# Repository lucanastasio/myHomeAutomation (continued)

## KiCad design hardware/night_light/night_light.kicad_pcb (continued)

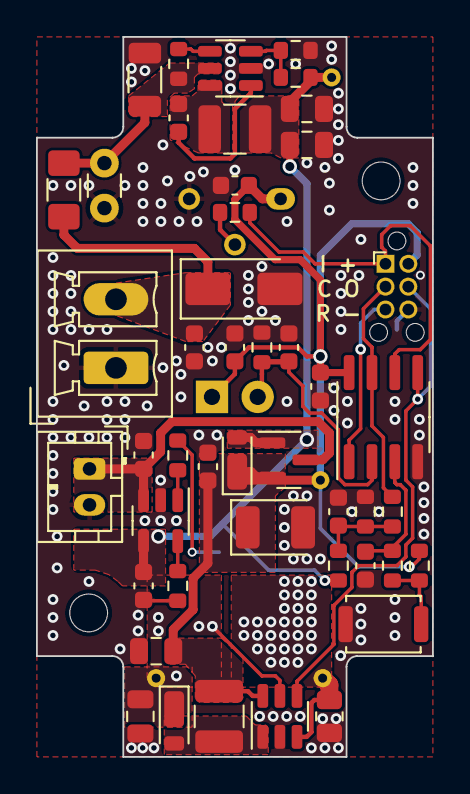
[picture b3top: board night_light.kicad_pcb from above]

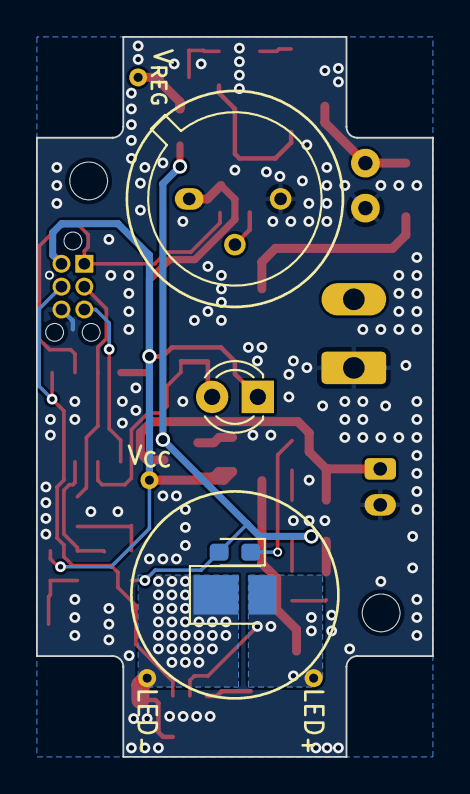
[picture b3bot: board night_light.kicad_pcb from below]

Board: 2 copper layers, 22.0 x 40.0 mm, 56 parts (8 on the bottom side), 25 nets.

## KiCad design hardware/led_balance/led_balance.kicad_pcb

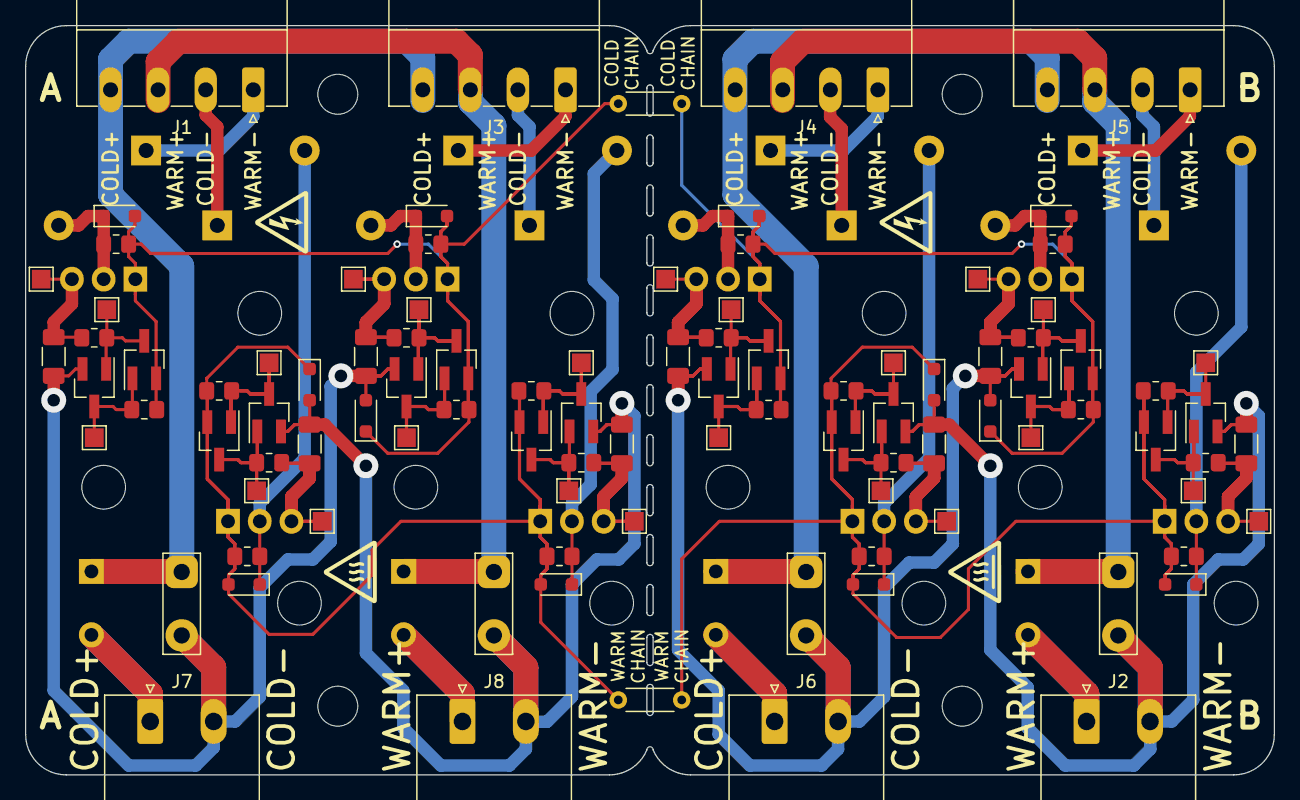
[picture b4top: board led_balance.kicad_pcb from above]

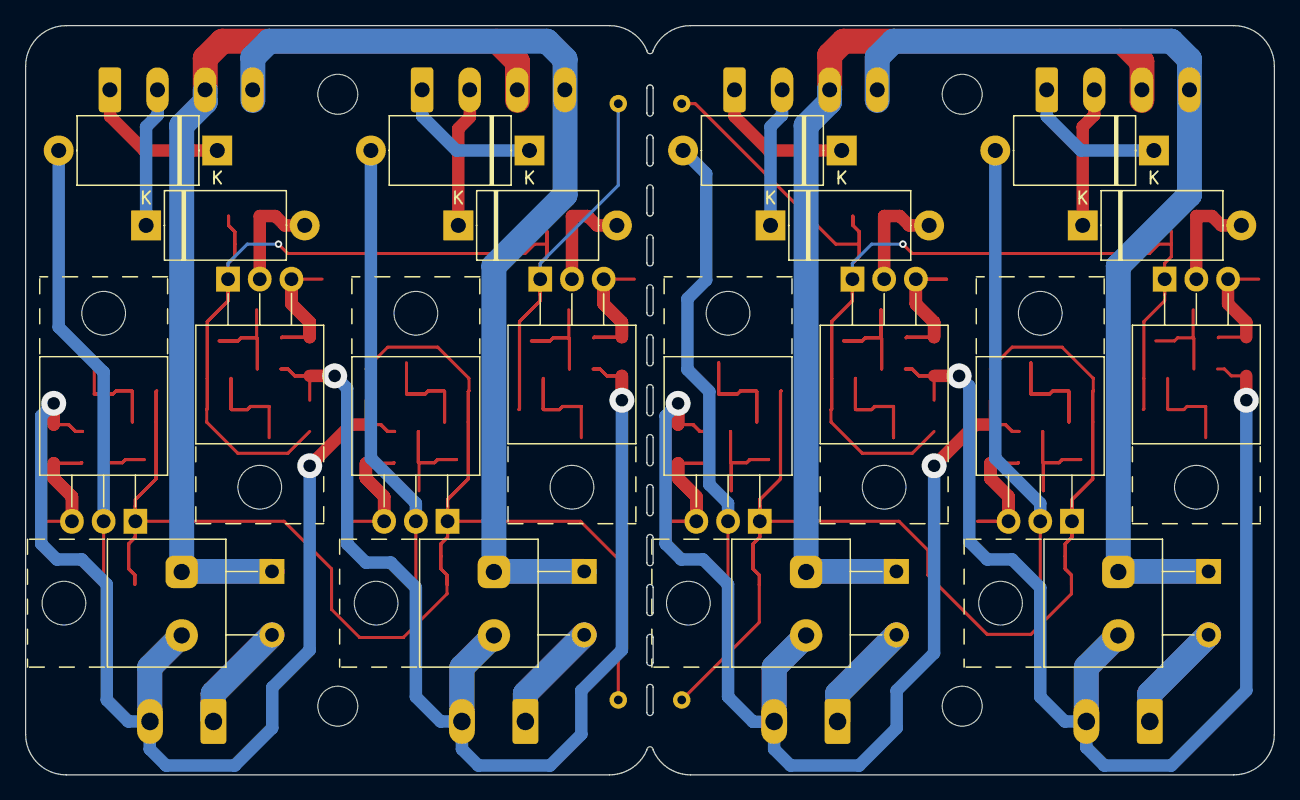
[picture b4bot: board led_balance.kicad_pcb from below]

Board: 2 copper layers, 100.0 x 60.0 mm, 126 parts (20 on the bottom side), 56 nets.

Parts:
D1, D4, D7, D10, D13, D16, D19, D22: 1N4148; D_SOD-323_HandSoldering
D2, D3, D5, D6: D_Zener; D_SOD-323_HandSoldering
D20, D21, D23, D24, D25, D26, D27, D28: 1N5333B; D_DO-27_P12.70mm_Horizontal
H1, H2, H3, H4: MountingHole; MountingHole_3.2mm_M3_DIN965
J1, J3, J4, J5: Screw_Terminal_01x04; PhoenixContact_MC_1,5_4-G-3.81_1x04_P3.81mm_Horizontal
J2, J6, J7, J8: Screw_Terminal_01x02; PhoenixContact_MSTBA_2,5_2-G-5,08_1x02_P5.08mm_Horizontal
Q1, Q2, Q3, Q4, Q5, Q6, Q7, Q8: Q_NMOS_GDS; TO-220-3_Horizontal_TabUp
Q17, Q19, Q21, Q23, Q25, Q27, Q29, Q31: Q_NPN_BEC; SOT-23_Handsoldering
Q18, Q20, Q22, Q24, Q26, Q28, Q30, Q32: Q_PNP_BEC; SOT-23_Handsoldering
R1, R3, R4, R6, R7, R9, R10, R12, R19, R21, R22, R24, R25, R27, R28, R30, R31, R32, R33, R34, R35, R36, R37, R38: R; R_0805_2012Metric_Pad1.20x1.40mm_HandSolder
R2, R5, R8, R11, R20, R23, R26, R29: R; R_1206_3216Metric_Pad1.30x1.75mm_HandSolder
R17, R18: R; R_Axial_DIN0204_L3.6mm_D1.6mm_P5.08mm_Horizontal
SYM1, SYM3: SYM_Hot_Small; Logo_silk_hot_5x4.2mm
SYM2, SYM4: SYM_Flash_Small; Logo_silk_high_voltage_5x4.2mm
TH1, TH2, TH3, TH4: Thermistor; TO-220-2_Horizontal_TabUp
TP5, TP6, TP7, TP8: TestPoint_2Pole; TestPoint_2Pads_Pitch5.08mm_Drill1.3mm
TP9, TP10, TP11, TP12, TP13, TP14, TP15, TP16, TP17, TP18, TP19, TP20, TP21, TP22, TP23, TP24, TP25, TP26, TP27, TP28, TP29, TP30, TP31, TP32: TestPoint; TestPoint_Pad_1.5x1.5mm

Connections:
/C0-: D25.1 (K), J1.2
/C1-: D26.1 (K), J3.2
/C2-: D27.1 (K), J4.2
/C3-: D28.1 (K), J5.2
/Ca: D2.1 (K), D13.2 (A), D16.2 (A), Q5.1 (G), Q6.1 (G), Q26.2 (E), Q28.2 (E), R17.1, R19.2, R22.2, R31.1, R33.1
/Ca+: J7.1, TH1.2
/Ca+i: J1.4, J3.4, TH1.1, TP5.1
/Ca-: D2.2 (A), J7.2, Q25.2 (E), Q27.2 (E), R20.2, R23.2, TP5.2
/Cb: D3.1 (K), D19.2 (A), D22.2 (A), Q7.1 (G), Q8.1 (G), Q30.2 (E), Q32.2 (E), R17.2, R25.2, R28.2, R35.1, R37.1
/Cb+: J6.1, TH3.2
/Cb+i: J4.4, J5.4, TH3.1, TP6.1
/Cb-: D3.2 (A), J6.2, Q29.2 (E), Q31.2 (E), R26.2, R29.2, TP6.2
/W0-: D20.1 (K), J1.1
/W1-: D21.1 (K), J3.1
/W2-: D23.1 (K), J4.1
/W3-: D24.1 (K), J5.1
/Wa: D1.2 (A), D4.2 (A), D5.1 (K), Q1.1 (G), Q2.1 (G), Q18.2 (E), Q20.2 (E), R1.2, R3.1, R4.2, R9.1, R18.1
/Wa+: J8.1, TH2.2
/Wa+i: J1.3, J3.3, TH2.1, TP7.1
/Wa-: D5.2 (A), J8.2, Q17.2 (E), Q19.2 (E), R2.2, R5.2, TP7.2
/Wb: D6.1 (K), D7.2 (A), D10.2 (A), Q3.1 (G), Q4.1 (G), Q22.2 (E), Q24.2 (E), R7.2, R10.2, R18.2, R21.1, R27.1
/Wb+: J2.1, TH4.2
/Wb+i: J4.3, J5.3, TH4.1, TP8.1
/Wb-: D6.2 (A), J2.2, Q21.2 (E), Q23.2 (E), R8.2, R11.2, TP8.2
unnamed: D1.1 (K), D20.2 (A), Q1.2 (D), R1.1
unnamed: D10.1 (K), D24.2 (A), Q4.2 (D), R10.1
unnamed: D13.1 (K), D25.2 (A), Q5.2 (D), R19.1
unnamed: D16.1 (K), D26.2 (A), Q6.2 (D), R22.1
unnamed: D19.1 (K), D27.2 (A), Q7.2 (D), R25.1
unnamed: D4.1 (K), D21.2 (A), Q2.2 (D), R4.1
unnamed: D22.1 (K), D28.2 (A), Q8.2 (D), R28.1
unnamed: D7.1 (K), D23.2 (A), Q3.2 (D), R7.1
unnamed: Q1.3 (S), R2.1, R6.1, TP11.1
unnamed: Q2.3 (S), R5.1, R12.1, TP14.1
unnamed: Q3.3 (S), R8.1, R24.1, TP17.1
unnamed: Q4.3 (S), R11.1, R30.1, TP20.1
unnamed: Q5.3 (S), R20.1, R32.1, TP23.1
unnamed: Q6.3 (S), R23.1, R34.1, TP26.1
unnamed: Q7.3 (S), R26.1, R36.1, TP29.1
unnamed: Q8.3 (S), R29.1, R38.1, TP32.1
unnamed: Q17.1 (B), Q18.3 (C), R6.2, TP10.1
unnamed: Q17.3 (C), Q18.1 (B), R3.2, TP9.1
unnamed: Q19.1 (B), Q20.3 (C), R12.2, TP13.1
unnamed: Q19.3 (C), Q20.1 (B), R9.2, TP12.1
unnamed: Q21.1 (B), Q22.3 (C), R24.2, TP16.1
unnamed: Q21.3 (C), Q22.1 (B), R21.2, TP15.1
unnamed: Q23.1 (B), Q24.3 (C), R30.2, TP19.1
unnamed: Q23.3 (C), Q24.1 (B), R27.2, TP18.1
unnamed: Q25.1 (B), Q26.3 (C), R32.2, TP22.1
unnamed: Q25.3 (C), Q26.1 (B), R31.2, TP21.1
unnamed: Q27.1 (B), Q28.3 (C), R34.2, TP25.1
unnamed: Q27.3 (C), Q28.1 (B), R33.2, TP24.1
unnamed: Q29.1 (B), Q30.3 (C), R36.2, TP28.1
unnamed: Q29.3 (C), Q30.1 (B), R35.2, TP27.1
unnamed: Q31.1 (B), Q32.3 (C), R38.2, TP31.1
unnamed: Q31.3 (C), Q32.1 (B), R37.2, TP30.1

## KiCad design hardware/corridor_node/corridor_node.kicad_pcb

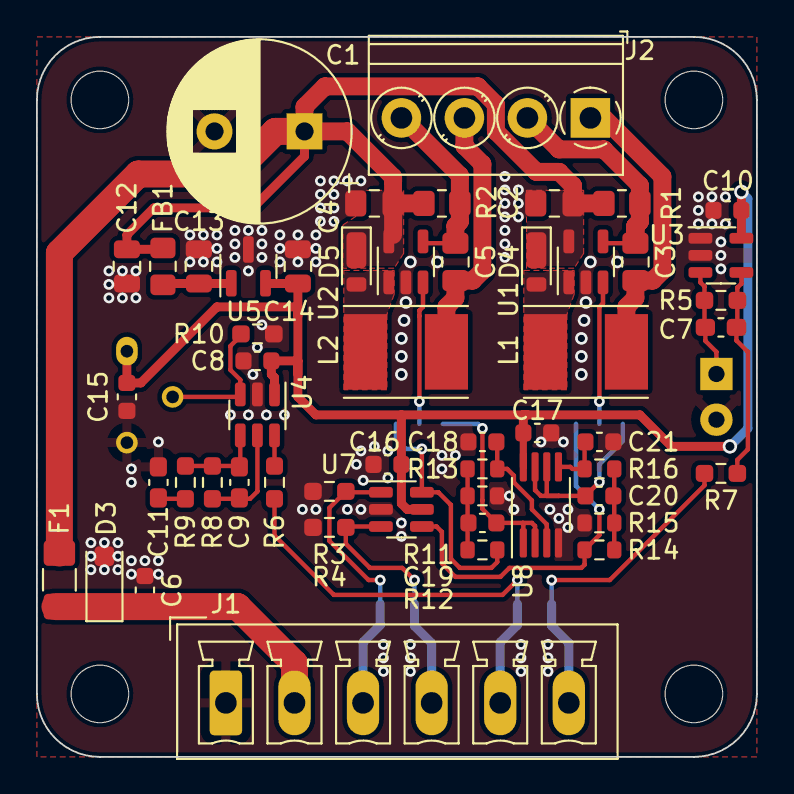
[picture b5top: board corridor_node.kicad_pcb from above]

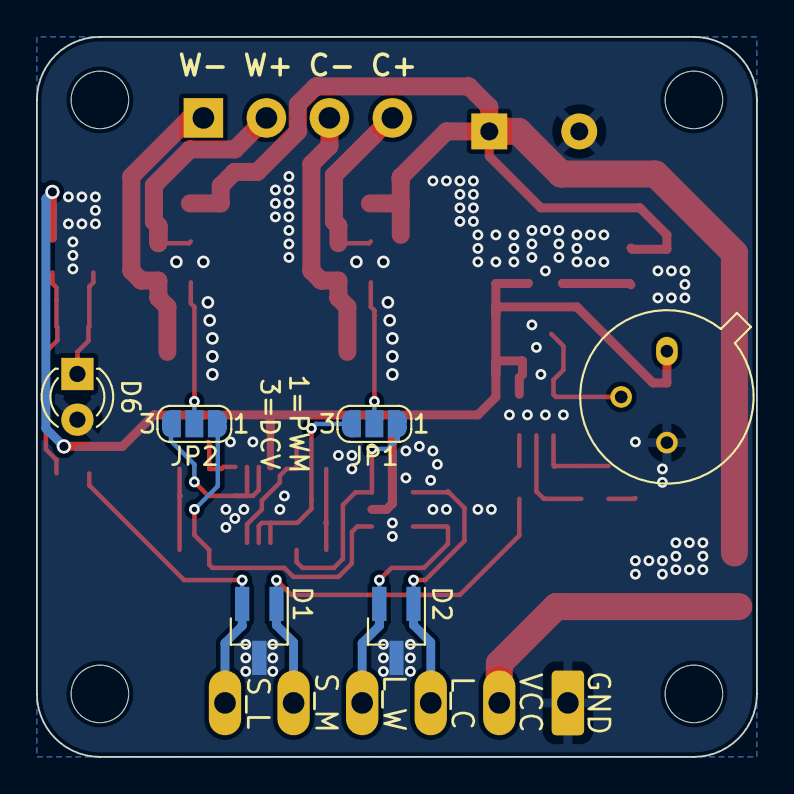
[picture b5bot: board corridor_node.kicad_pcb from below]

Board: 2 copper layers, 40.0 x 40.0 mm, 63 parts (6 on the bottom side), 32 nets.

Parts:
C1: 470uF 50V; CP_Radial_D10.0mm_P5.00mm
C2, C3, C4, C5: 10u 50V; C_0805_2012Metric_Pad1.18x1.45mm_HandSolder
C6: 1n 1kV; C_0603_1608Metric
C7, C9: 100n 50V; C_0603_1608Metric_Pad1.08x0.95mm_HandSolder
C8, C10, C15, C16, C17, C18, C19, C20, C21: 100n 50V; C_0603_1608Metric
C11: 10u 16V; C_0603_1608Metric_Pad1.08x0.95mm_HandSolder
C12, C13: 10u 50V; C_0805_2012Metric
C14: 22u 10V; C_0805_2012Metric
D1, D2: SM05; SOT-23_Handsoldering
D3: SMF36A; D_SOD-123F
D4, D5: RB160VA-40TR; D_TUMD2
D6: TEPT5700; LED_D3.0mm_Clear
F1: 500mA; Fuse_1206_3216Metric_Pad1.42x1.75mm_HandSolder
FB1: MMZ2012R102AT000; L_0805_2012Metric_Pad1.15x1.40mm_HandSolder
H1, H2, H3, H4: MountingHole; MountingHole_3.2mm_M3
J1: Screw_Terminal_01x06; PhoenixContact_MCV_1,5_6-G-3.81_1x06_P3.81mm_Vertical
J2: Screw_Terminal_01x04; TerminalBlock_Phoenix_PT-1,5-4-3.5-H_1x04_P3.50mm_Horizontal
JP1, JP2: SolderJumper_3_Open; SolderJumper-3_P1.3mm_Open_RoundedPad1.0x1.5mm_NumberLabels
L1, L2: 100uH; L_Taiyo-Yuden_NR-50xx_HandSoldering
R1, R2: 0.4; R_0805_2012Metric_Pad1.20x1.40mm_HandSolder
R3, R4: 1k; R_0603_1608Metric_Pad0.98x0.95mm_HandSolder
R5: 1M; R_0603_1608Metric_Pad0.98x0.95mm_HandSolder
R6, R7: 100; R_0603_1608Metric_Pad0.98x0.95mm_HandSolder
R8: 2M; R_0603_1608Metric_Pad0.98x0.95mm_HandSolder
R9: 10k; R_0603_1608Metric_Pad0.98x0.95mm_HandSolder
R10: 47k; R_0603_1608Metric_Pad0.98x0.95mm_HandSolder
R11, R12, R13, R14, R15, R16: 100k; R_0603_1608Metric
U1, U2: SD3361; SOT-23-5
U3: LMV321; SOT-23-5
U4: TTY020-CA6; SOT-23-6
U5: AP7384-50SA; SOT-23
U6: PIR; TO-5-3_Window
U7: 74LVC2G17; SOT-23-6
U8: LMV358; MSOP-8_3x3mm_P0.65mm

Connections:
+5V: C8.1, C10.1, C14.1, C15.1, C16.1, C17.1, U3.5 (V+), U4.1 (VDD), U5.2 (VO), U6.1, U7.5 (VCC), U8.8 (V+)
+36V: C1.1, C2.1, C4.1, C12.2, D4.1 (K), D5.1 (K), F1.2, FB1.1, R1.1, R2.1, U1.5 (VIN), U2.5 (VIN)
/C+: C5.1, J2.4, R2.2, U2.4 (ISENSE)
/C-: C5.2, J2.3, L2.2
/LED_C: D2.1 (A1), J1.3, R3.2, U7.1
/LED_W: D2.2 (A2), J1.4, R4.2, U7.3
/PWM to DC/OUT0: JP1.2 (C), U2.3 (VSET)
/PWM to DC/OUT1: JP2.2 (C), U1.3 (VSET)
/PWM to DC/PWM0: JP1.1 (A), R12.1, U7.6
/PWM to DC/PWM0A: C19.2, R11.1, R12.2, R13.1
/PWM to DC/PWM0B: C18.1, R13.2, U8.3 (+)
/PWM to DC/PWM1: JP2.1 (A), R14.1, U7.4
/PWM to DC/PWM1A: C20.1, R14.2, R15.1, R16.1
/PWM to DC/PWM1B: C21.1, R16.2, U8.5 (+)
/SEN_L: D1.2 (A2), J1.6, R7.1
/SEN_M: D1.1 (A1), J1.5, R6.1
/W+: C3.1, J2.2, R1.2, U1.4 (ISENSE)
/W-: C3.2, J2.1, L1.2
/driver 0/LX: D5.2 (A), L2.1, U2.1 (LX)
/driver 1/LX: D4.2 (A), L1.1, U1.1 (LX)
/sensors/ALS: C7.2, R5.2, R7.2, U3.4
/sensors/OP_N: C9.1, R8.1, R9.1, U4.4 (OP_N)
/sensors/OP_O: C9.2, R8.2, U4.5 (OP_O)
/sensors/OP_P: R10.2, U4.3 (OP_P), U6.2
/sensors/PIR: R6.2, U4.6 (OUTN)
/sensors/PT-: C7.1, D6.1 (K), R5.1, U3.3 (-)
GND: C1.2, C2.2, C4.2, C6.2, C8.2, C10.2, C11.1, C12.1, C13.2, C14.2, C15.2, C16.2, C17.2, C18.2, C21.2, D1.3 (common), D2.3 (common), D3.2 (A), D6.2 (A), J1.1, R3.1, R4.1, R10.1, R11.2, R15.2, U1.2 (GND), U2.2 (GND), U3.1 (+), U3.2 (V-), U4.2 (VSS), U5.3 (GND), U6.3, U7.2 (GND), U8.4 (V-)
unnamed: C11.2, R9.2
unnamed: C19.1, JP1.3 (B), U8.1, U8.2 (-)
unnamed: C20.2, JP2.3 (B), U8.6 (-), U8.7
unnamed: C13.1, FB1.2, U5.1 (VI)
VCC: C6.1, D3.1 (K), F1.1, J1.2

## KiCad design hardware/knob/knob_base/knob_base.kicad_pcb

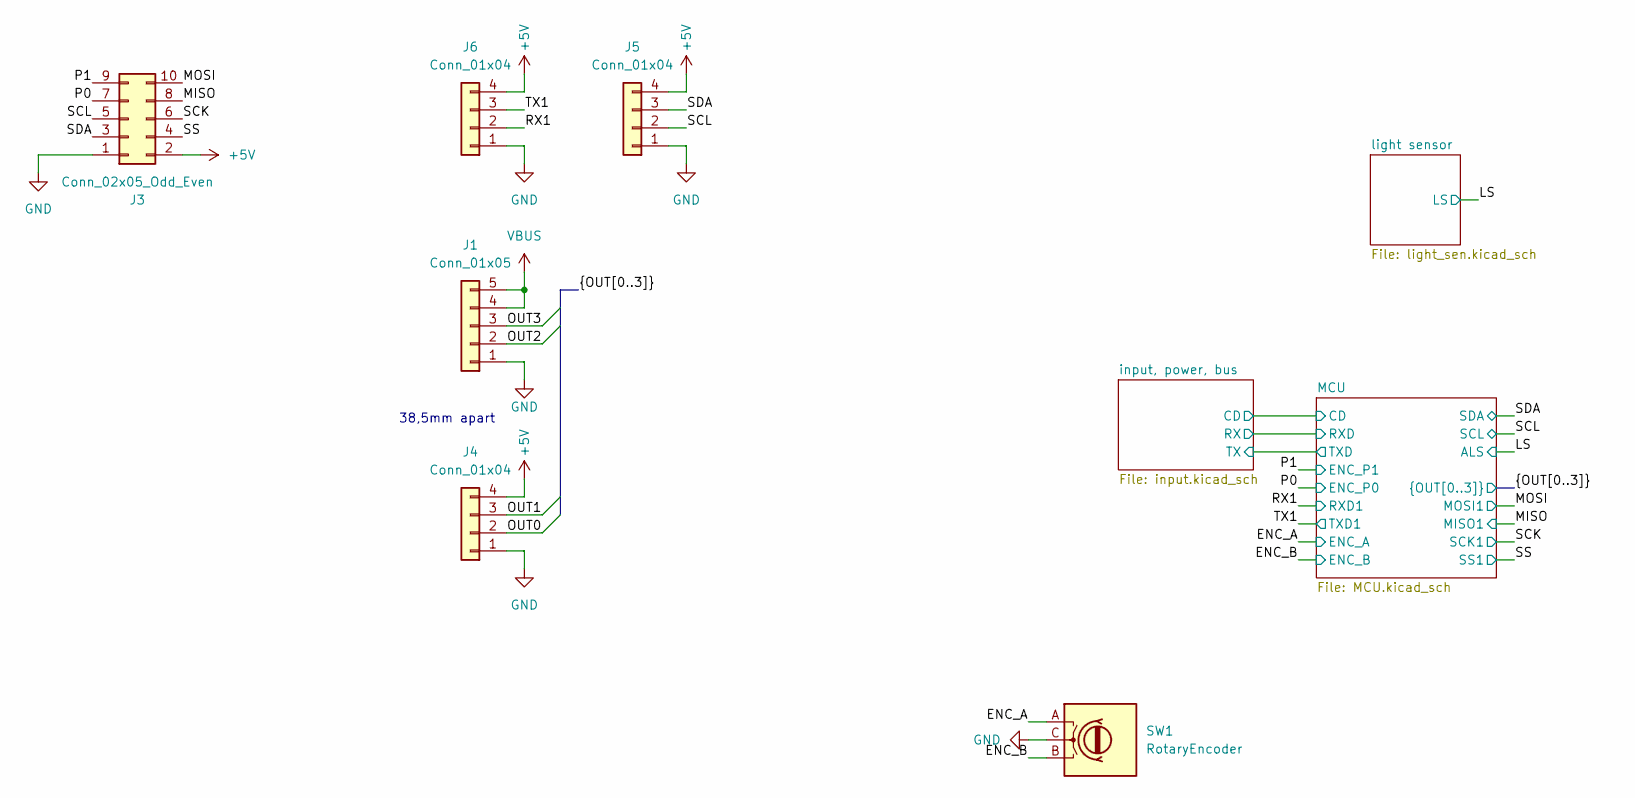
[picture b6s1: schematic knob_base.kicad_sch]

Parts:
J1: Conn_01x05; PinSocket_1x05_P2.54mm_Vertical
J3: Conn_02x05_Odd_Even; PinSocket_2x05_P2.54mm_Vertical_SMD
J4: Conn_01x04; PinSocket_1x04_P2.54mm_Vertical
J5, J6: Conn_01x04; JST_PH_B4B-PH-K_1x04_P2.00mm_Vertical
SW1: RotaryEncoder; EC35A0930401

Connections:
+5V: J3.2, J4.4, J5.4, J6.4; also elsewhere on the board
/ENC_A: SW1.A; also elsewhere on the board
/ENC_B: SW1.B; also elsewhere on the board
/MISO: J3.8; also elsewhere on the board
/MOSI: J3.10; also elsewhere on the board
/OUT0: J4.2; also elsewhere on the board
/OUT1: J4.3; also elsewhere on the board
/OUT2: J1.2; also elsewhere on the board
/OUT3: J1.3; also elsewhere on the board
/P0: J3.7; also elsewhere on the board
/P1: J3.9; also elsewhere on the board
/RX1: J6.2; also elsewhere on the board
/SCK: J3.6; also elsewhere on the board
/SCL: J3.5, J5.2; also elsewhere on the board
/SDA: J3.3, J5.3; also elsewhere on the board
/SS: J3.4; also elsewhere on the board
/TX1: J6.3; also elsewhere on the board
GND: J1.1, J3.1, J4.1, J5.1, J6.1, SW1.C; also elsewhere on the board
VBUS: J1.4, J1.5; also elsewhere on the board

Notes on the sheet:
38,5mm apart

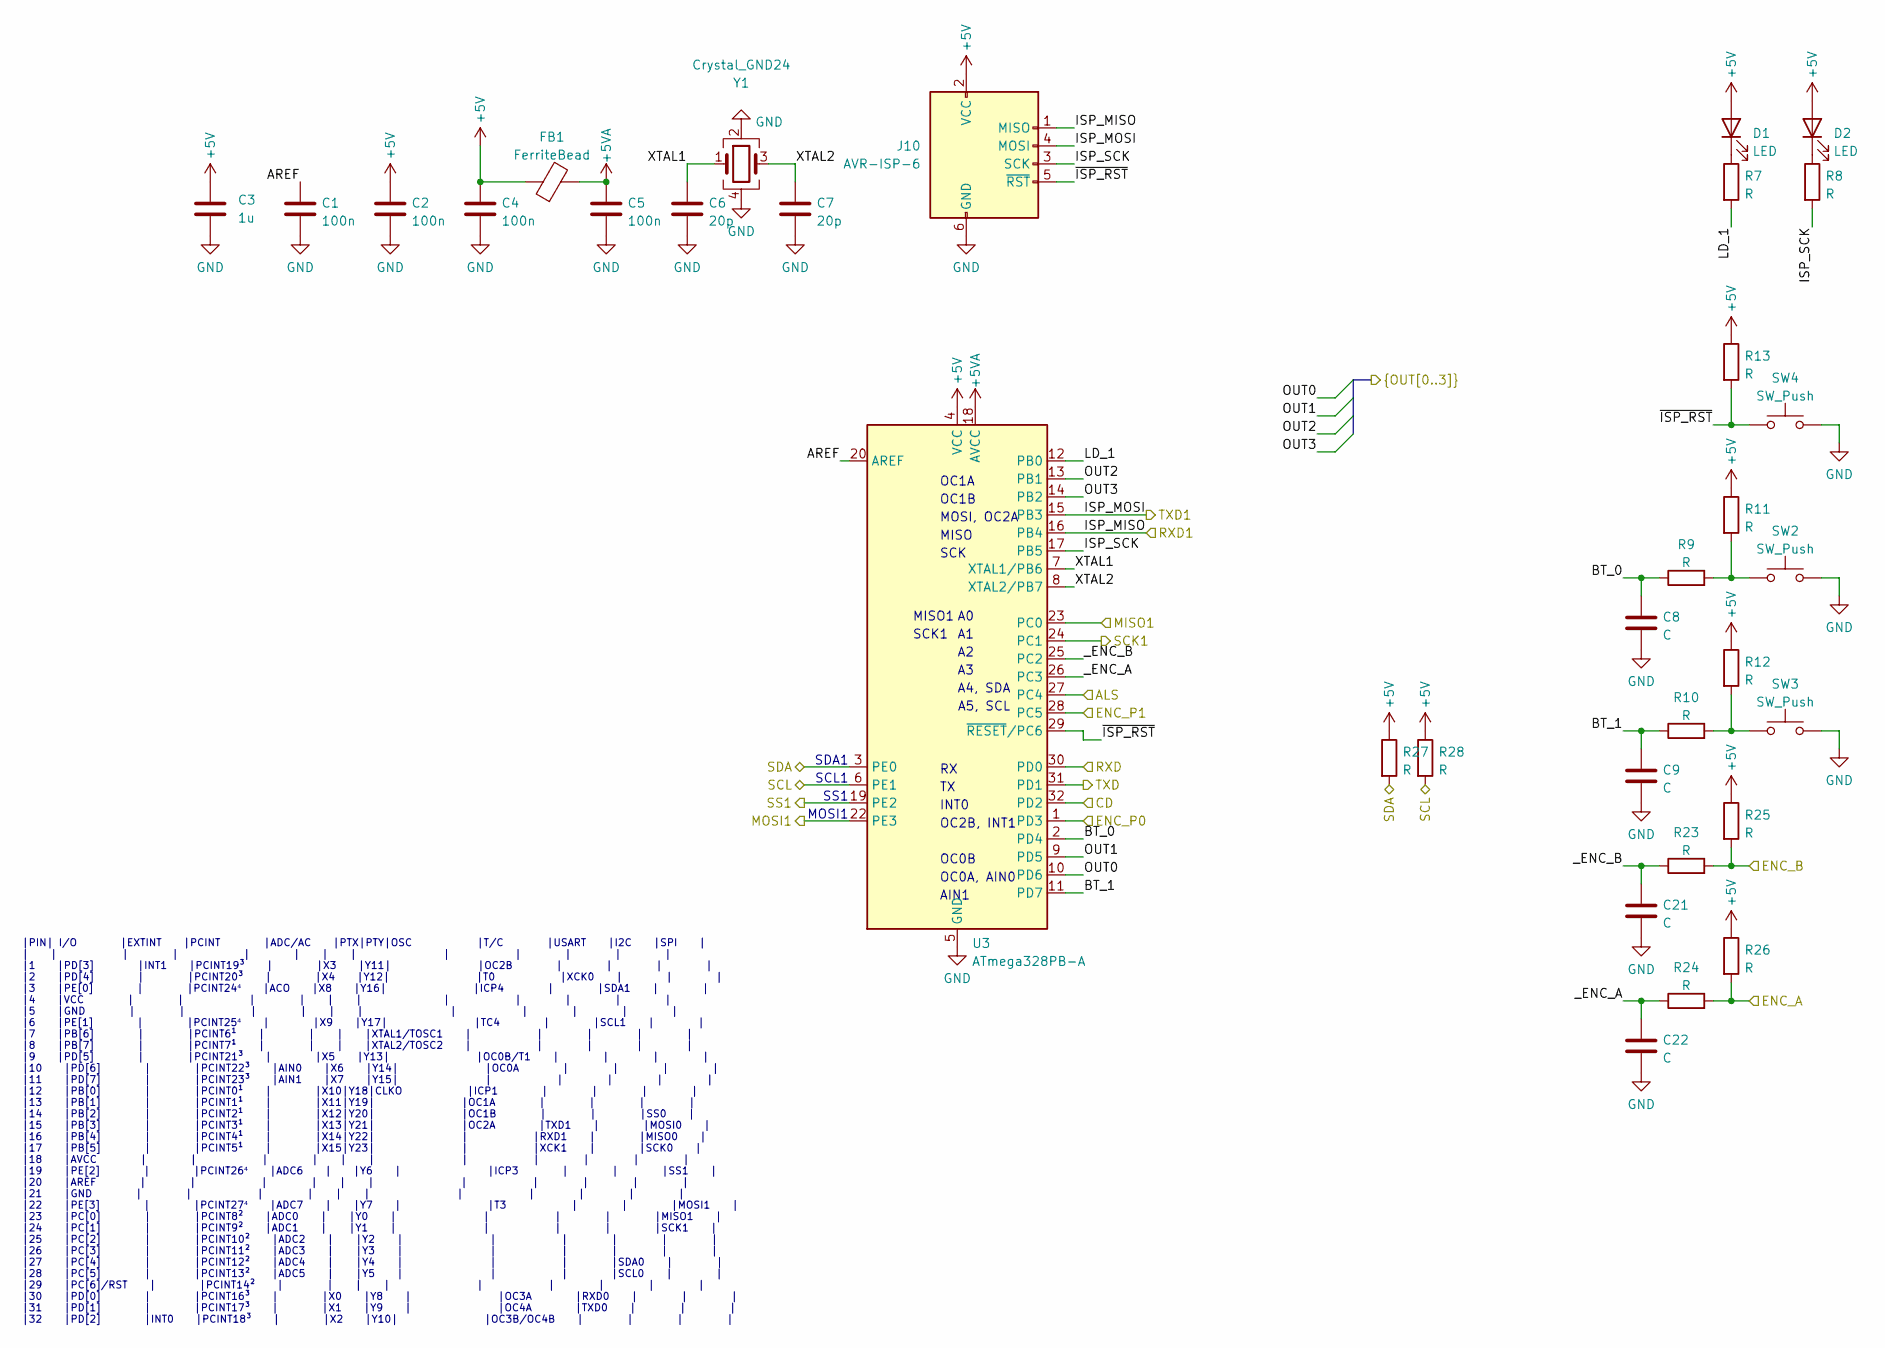
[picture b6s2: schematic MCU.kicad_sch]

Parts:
C1, C2, C4, C5: 100n; C_0603_1608Metric
C3: 1u; C_0603_1608Metric
C6, C7: 20p; C_0603_1608Metric
C8, C9, C21, C22: C; C_0603_1608Metric
D1, D2: LED; LED_0603_1608Metric
FB1: FerriteBead; L_0603_1608Metric
J10: AVR-ISP-6; Tag-Connect_TC2030-IDC-NL_2x03_P1.27mm_Vertical
R7, R8, R9, R10, R11, R12, R13, R23, R24, R25, R26, R27, R28: R; R_0603_1608Metric
SW2, SW3, SW4: SW_Push; SW_SPST_B3U-1000P
U3: ATmega328PB-A; TQFP-32_7x7mm_P0.8mm
Y1: Crystal_GND24; Crystal_SMD_3225-4Pin_3.2x2.5mm

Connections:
+5V: C2.2, C3.2, C4.1, D1.2 (A), D2.2 (A), FB1.1, J10.2 (VCC), R11.1, R12.1, R13.1, R25.1, R26.1, R27.1, R28.1, U3.4 (VCC); also elsewhere on the board
+5VA: C5.1, FB1.2, U3.18 (AVCC); also elsewhere on the board
/ENC_A: R24.2, R26.2; also elsewhere on the board
/ENC_B: R23.2, R25.2; also elsewhere on the board
/LS: U3.27 (PC4); also elsewhere on the board
/MCU/AREF: C1.1, U3.20 (AREF)
/MCU/BT_0: C8.1, R9.1, U3.2 (PD4)
/MCU/BT_1: C9.1, R10.1, U3.11 (PD7)
/MCU/CD: U3.32 (PD2); also elsewhere on the board
/MCU/ISP_SCK: J10.3 (SCK), R8.2, U3.17 (PB5)
/MCU/LD_1: R7.2, U3.12 (PB0)
/MCU/RXD: U3.30 (PD0); also elsewhere on the board
/MCU/TXD: U3.31 (PD1); also elsewhere on the board
/MCU/XTAL1: C6.1, U3.7 (XTAL1/PB6), Y1.1
/MCU/XTAL2: C7.1, U3.8 (XTAL2/PB7), Y1.3
/MCU/_ENC_A: C22.1, R24.1, U3.26 (PC3)
/MCU/_ENC_B: C21.1, R23.1, U3.25 (PC2)
/MCU/~ISP_RST: J10.5 (~RST), R13.2, SW4.1, U3.29 (~RESET/PC6)
/MISO: U3.23 (PC0); also elsewhere on the board
/MOSI: U3.22 (PE3); also elsewhere on the board
/OUT0: U3.10 (PD6); also elsewhere on the board
/OUT1: U3.9 (PD5); also elsewhere on the board
/OUT2: U3.13 (PB1); also elsewhere on the board
/OUT3: U3.14 (PB2); also elsewhere on the board
/P0: U3.1 (PD3); also elsewhere on the board
/P1: U3.28 (PC5); also elsewhere on the board
/RX1: J10.1 (MISO), U3.16 (PB4); also elsewhere on the board
/SCK: U3.24 (PC1); also elsewhere on the board
/SCL: R28.2, U3.6 (PE1); also elsewhere on the board
/SDA: R27.2, U3.3 (PE0); also elsewhere on the board
/SS: U3.19 (PE2); also elsewhere on the board
/TX1: J10.4 (MOSI), U3.15 (PB3); also elsewhere on the board
GND: C1.2, C2.1, C3.1, C4.2, C5.2, C6.2, C7.2, C8.2, C9.2, C21.2, C22.2, J10.6 (GND), SW2.2, SW3.2, SW4.2, U3.5 (GND), U3.21 (GND), Y1.2, Y1.4; also elsewhere on the board
unnamed: D1.1 (K), R7.1
unnamed: D2.1 (K), R8.1
unnamed: R10.2, R12.2, SW3.1
unnamed: R9.2, R11.2, SW2.1

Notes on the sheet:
OC0B
OC1B
SS1
OC1A
MISO
SCK1
|PIN| I/O |EXTINT |PCINT |ADC/AC |PTX|PTY|OSC |T/C |USART |I2C |SPI | | | | | | | | | | | | | | |1 |PD[3] |INT1 |PCINT19³ | |X3 |Y11| |OC2B | | | | |2 |PD[4] | |PCINT20³ | |X4 |Y12| |T0 |XCK0 | | | |3 |PE[0] | |PCINT24⁴ |ACO |X8 |Y16| |ICP4 | |SDA1 | | |4 |VCC | | | | | | | | | | | |5 |GND | | | | 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
SCL1
A4, SDA
OC2B, INT1
SDA1
INT0
OC0A, AIN0
MOSI, OC2A
SCK
MISO1
AIN1
A5, SCL
MOSI1

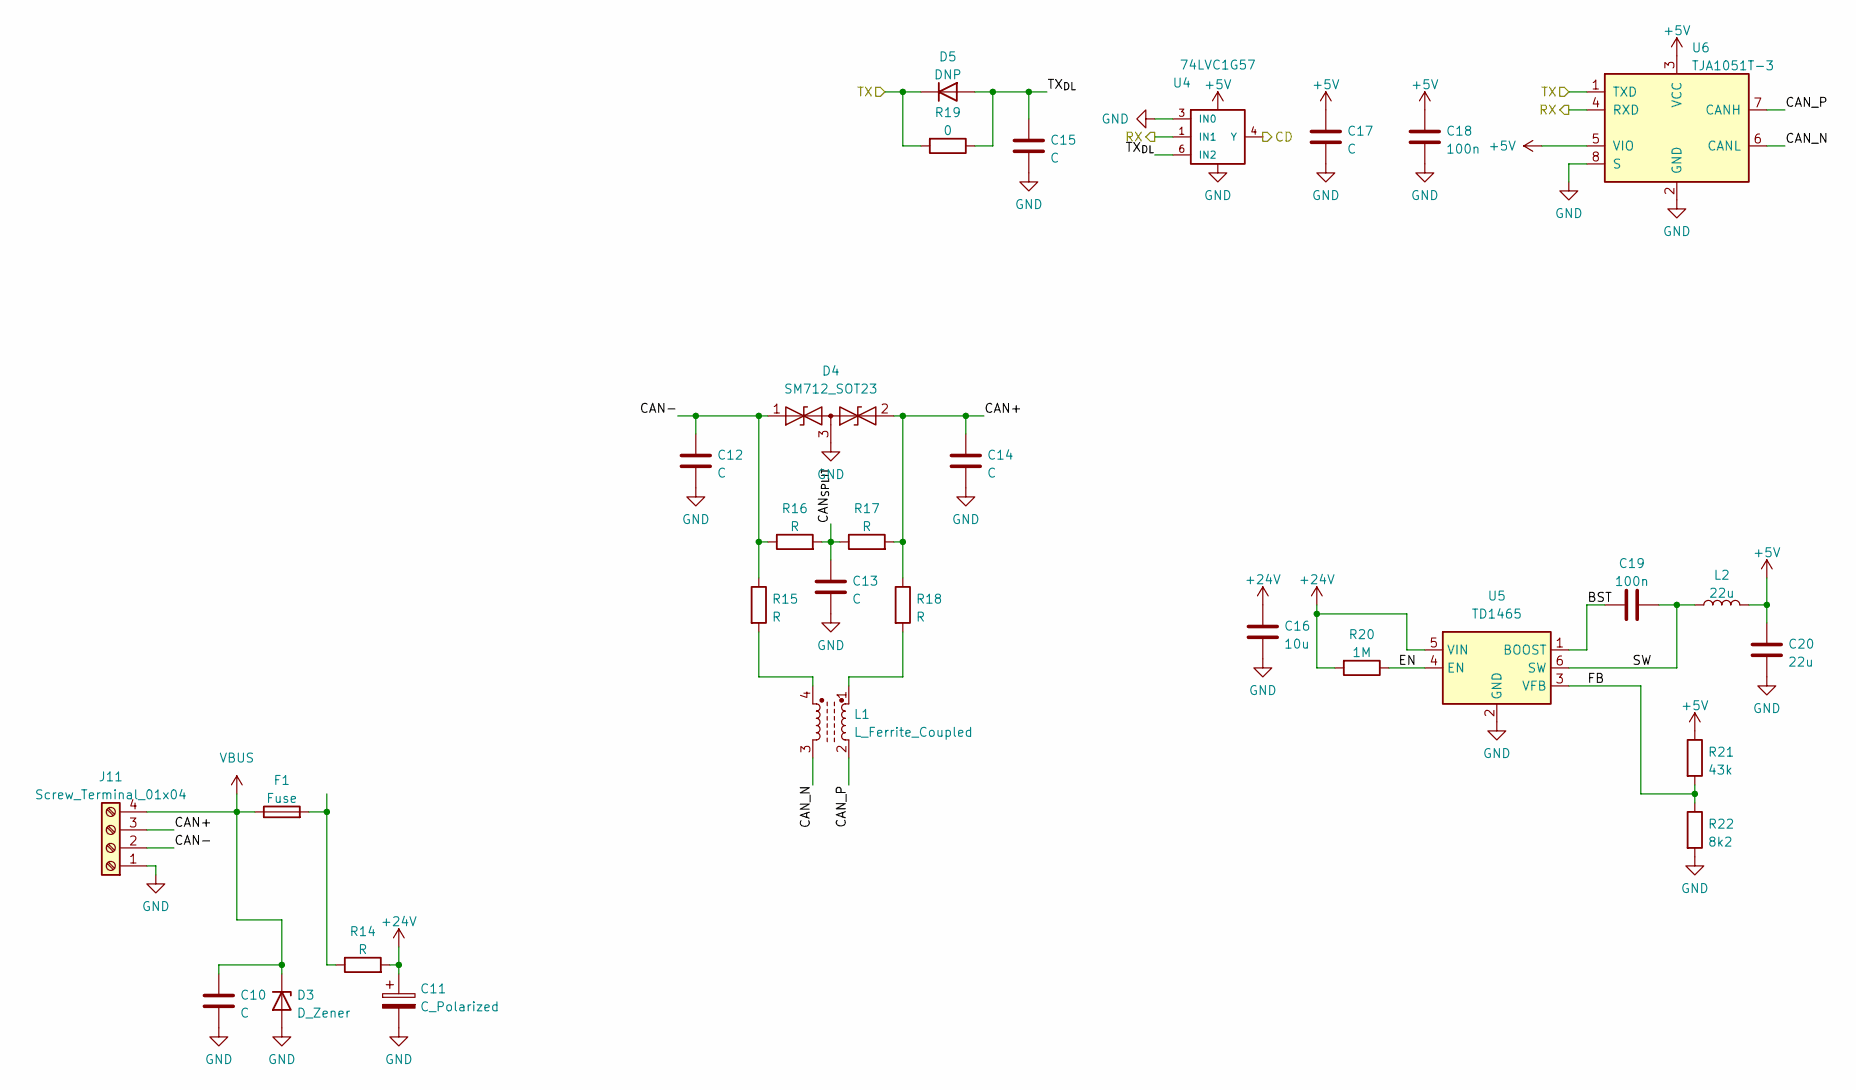
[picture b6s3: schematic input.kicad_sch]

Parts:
C10, C12, C14, C15, C17: C; C_0603_1608Metric
C11: C_Polarized; CP_Radial_D6.3mm_P2.50mm
C13: C; C_0805_2012Metric_Pad1.18x1.45mm_HandSolder
C16: 10u; C_1206_3216Metric
C18, C19: 100n; C_0603_1608Metric
C20: 22u; C_0805_2012Metric
D3: D_Zener; D_SMA
D4: SM712_SOT23; SOT-23
D5: DNP; D_SOD-523
F1: Fuse; Fuse_0805_2012Metric_Pad1.15x1.40mm_HandSolder
J11: Screw_Terminal_01x04; PhoenixContact_MCV_1,5_4-G-3.81_1x04_P3.81mm_Vertical
L1: L_Ferrite_Coupled; L_CommonModeChoke_Coilcraft_0805USB
L2: 22u; L_1210_3225Metric
R14: R; R_0805_2012Metric
R15, R18: R; R_0603_1608Metric
R16, R17: R; R_0805_2012Metric_Pad1.20x1.40mm_HandSolder
R19: 0; R_0603_1608Metric
R20: 1M; R_0603_1608Metric
R21: 43k; R_0603_1608Metric
R22: 8k2; R_0603_1608Metric
U4: 74LVC1G57; SOT-363_SC-70-6
U5: TD1465; SOT-23-6
U6: TJA1051T-3; SOIC-8_3.9x4.9mm_P1.27mm

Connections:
+5V: C17.1, C18.2, C20.2, L2.2, R21.1, U4.5 (VCC), U6.3 (VCC), U6.5 (VIO); also elsewhere on the board
+24V: C11.1, C16.2, R14.2, R20.2, U5.5 (VIN)
/MCU/CD: U4.4 (Y); also elsewhere on the board
/MCU/RXD: U4.1 (IN1), U6.4 (RXD); also elsewhere on the board
/MCU/TXD: D5.1 (K), R19.2, U6.1 (TXD); also elsewhere on the board
/input, power, bus/BST: C19.1, U5.1 (BOOST)
/input, power, bus/CAN+: C14.1, D4.2 (A2), J11.3, R17.2, R18.1
/input, power, bus/CAN-: C12.1, D4.1 (A1), J11.2, R15.1, R16.1
/input, power, bus/CAN_N: L1.3, U6.6 (CANL)
/input, power, bus/CAN_P: L1.2, U6.7 (CANH)
/input, power, bus/CAN_{SPLIT}: C13.1, R16.2, R17.1
/input, power, bus/EN: R20.1, U5.4 (EN)
/input, power, bus/FB: R21.2, R22.1, U5.3 (VFB)
/input, power, bus/SW: C19.2, L2.1, U5.6 (SW)
/input, power, bus/TX_{DL}: C15.1, D5.2 (A), R19.1, U4.6 (IN2)
GND: C10.2, C11.2, C12.2, C13.2, C14.2, C15.2, C16.1, C17.2, C18.1, C20.1, D3.2 (A), D4.3 (common), J11.1, R22.2, U4.2 (GND), U4.3 (IN0), U5.2 (GND), U6.2 (GND), U6.8 (S); also elsewhere on the board
unnamed: F1.2, R14.1
unnamed: L1.1, R18.2
unnamed: L1.4, R15.2
VBUS: C10.1, D3.1 (K), F1.1, J11.4; also elsewhere on the board

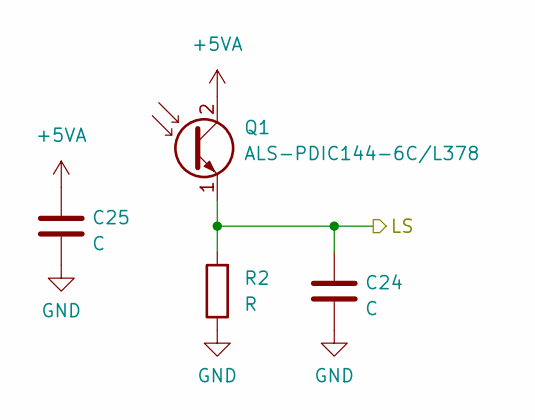
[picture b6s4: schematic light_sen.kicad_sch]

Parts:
C24, C25: C; C_0603_1608Metric
Q1: ALS-PDIC144-6C/L378; LED_D3.0mm_FlatTop
R2: R; R_0603_1608Metric

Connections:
+5VA: C25.2, Q1.2 (C); also elsewhere on the board
/LS: C24.2, Q1.1 (E), R2.2; also elsewhere on the board
GND: C24.1, C25.1, R2.1; also elsewhere on the board

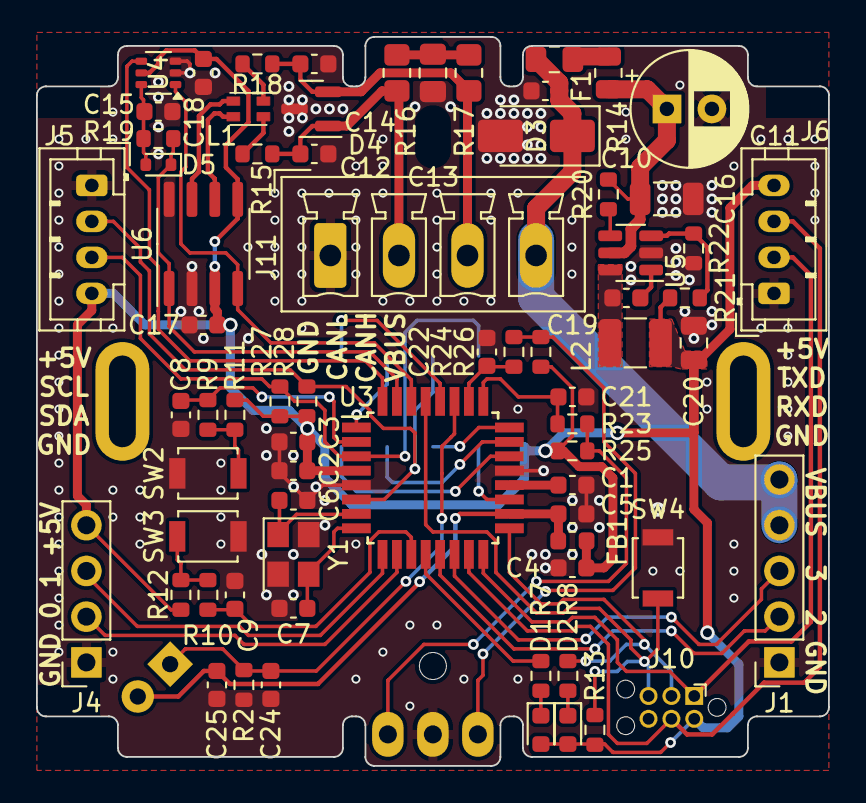
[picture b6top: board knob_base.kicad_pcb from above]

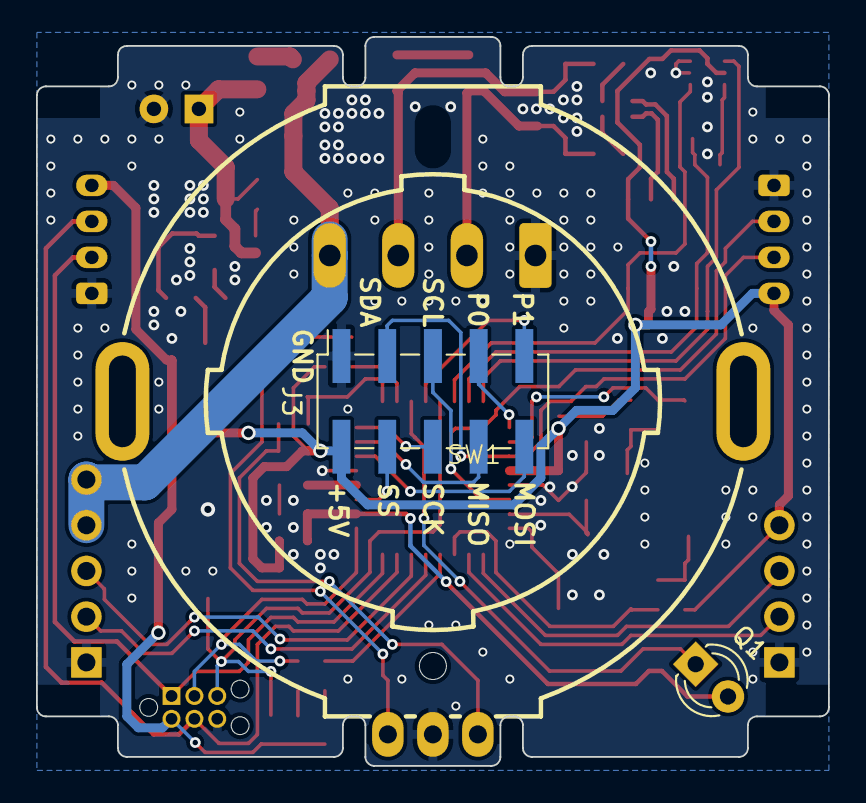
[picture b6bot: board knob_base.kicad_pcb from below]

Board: 2 copper layers, 44.0 x 40.5 mm, 73 parts (3 on the bottom side), 52 nets.

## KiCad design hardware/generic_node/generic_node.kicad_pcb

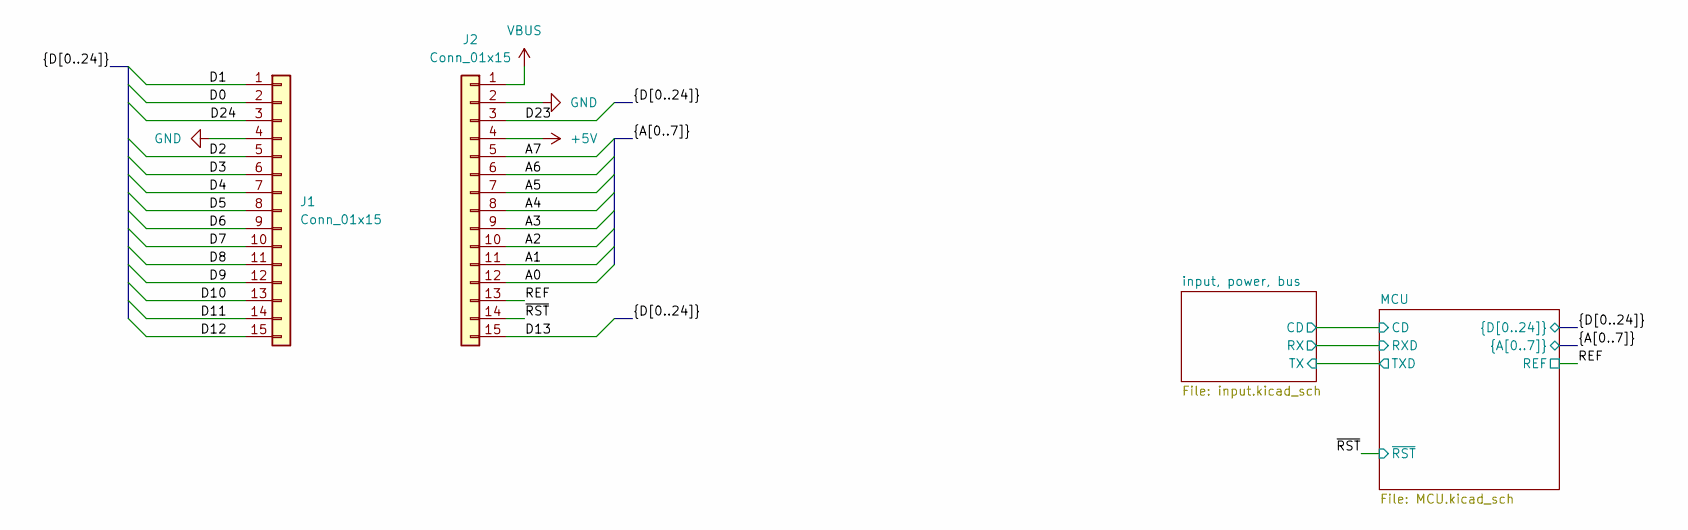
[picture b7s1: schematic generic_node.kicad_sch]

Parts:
J1, J2: Conn_01x15; PinHeader_1x15_P2.54mm_Vertical

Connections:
+5V: J2.4; also elsewhere on the board
/A0: J2.12; also elsewhere on the board
/A1: J2.11; also elsewhere on the board
/A2: J2.10; also elsewhere on the board
/A3: J2.9; also elsewhere on the board
/A4: J2.8; also elsewhere on the board
/A5: J2.7; also elsewhere on the board
/A6: J2.6; also elsewhere on the board
/A7: J2.5; also elsewhere on the board
/D0: J1.2; also elsewhere on the board
/D1: J1.1; also elsewhere on the board
/D2: J1.5; also elsewhere on the board
/D3: J1.6; also elsewhere on the board
/D4: J1.7; also elsewhere on the board
/D5: J1.8; also elsewhere on the board
/D6: J1.9; also elsewhere on the board
/D7: J1.10; also elsewhere on the board
/D8: J1.11; also elsewhere on the board
/D9: J1.12; also elsewhere on the board
/D10: J1.13; also elsewhere on the board
/D11: J1.14; also elsewhere on the board
/D12: J1.15; also elsewhere on the board
/D13: J2.15; also elsewhere on the board
/D23: J2.3; also elsewhere on the board
/D24: J1.3; also elsewhere on the board
/REF: J2.13; also elsewhere on the board
/~RST: J2.14; also elsewhere on the board
GND: J1.4, J2.2; also elsewhere on the board
VBUS: J2.1; also elsewhere on the board
